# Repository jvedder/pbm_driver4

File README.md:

# pdm_driver4_v1

PCB Design in KiCad 7 with 4 channels of high-speed, current-controlled LED drivers for a PBM Device prototype. 

**MIT License**

**WARNING**: The eye safety of this device has not been established. **USE AT YOUR OWN RISK.**

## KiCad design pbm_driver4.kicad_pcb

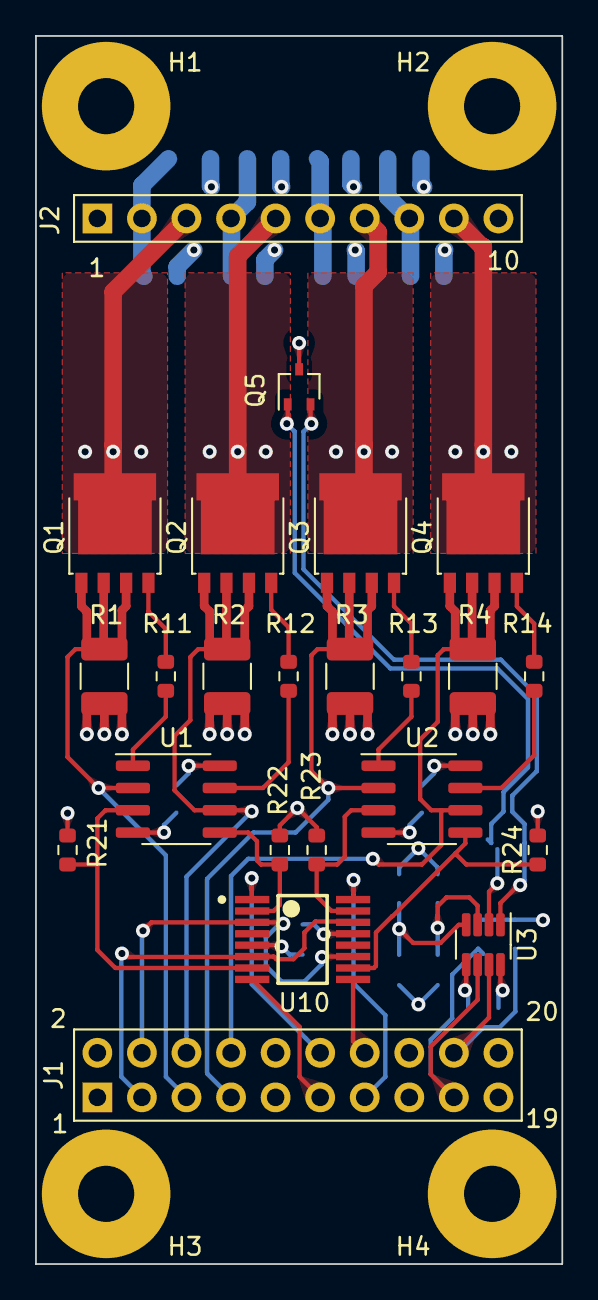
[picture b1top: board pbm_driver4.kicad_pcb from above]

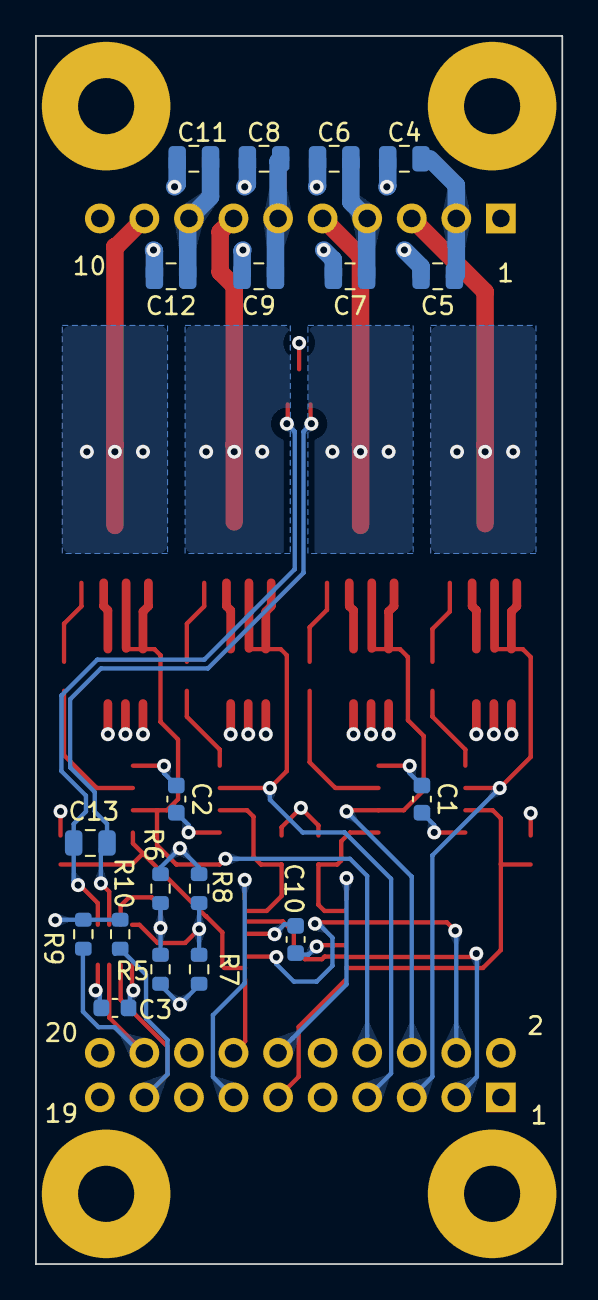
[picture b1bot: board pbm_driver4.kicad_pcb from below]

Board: 4 copper layers, 30.0 x 70.0 mm, 46 parts (19 on the bottom side), 35 nets.

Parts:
C1, C2, C3, C10: 0.1uF; C_0603_1608Metric
C4, C5, C6, C7, C8, C9, C11, C12: 10uF; C_0805_2012Metric
C13: 100pF; C_0805_2012Metric
H1, H2, H3, H4: MountingHole_Pad; MountingHole_3.2mm_M3_Pad
J1: Conn_02x10_Odd_Even; PinHeader_2x10_P2.54mm_Vertical
J2: Conn_01x10; PinHeader_1x10_P2.54mm_Vertical
Q1, Q2, Q3, Q4: PSMN4R0-30YLD; LFPAK56
Q5: MMBT3906; SOT-323_SC-70
R1, R2, R3, R4: 0.510; R_1210_3225Metric_Pad1.30x2.65mm_HandSolder
R5, R6, R7, R8, R9, R10: 10K; R_0603_1608Metric
R11, R12, R13, R14: 100; R_0603_1608Metric
R21, R22, R23, R24: 100K; R_0603_1608Metric
U1, U2: ADA4099-2; SOIC-8_3.9x4.9mm_P1.27mm
U3: TMP421; SOT-23-8
U10: TMUX1112PWR; PW0016A-IPC_A

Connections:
+3.3V: C3.1, C10.1, J1.20, R5.1, R7.1, R9.1, R10.1, U3.8 (V+), U10.13 (VDD)
+12V: C1.1, C2.1, C4.1, C5.1, C6.1, C7.1, C8.1, C9.1, C11.1, C12.1, J1.2, J2.2, J2.4, J2.6, J2.8, U1.8 (V+), U2.8 (V+)
/DAC1: J1.3, U10.6 (S4), U10.14 (S2)
/DAC2: J1.4, U10.3 (S1), U10.11 (S3)
/I2C_SCL: J1.17, R10.2, U3.6 (SDA)
/I2C_SDA: J1.18, R9.2, U3.7 (SCL)
/LED1: J2.3, Q1.5 (D)
/LED2: J2.5, Q2.5 (D)
/LED3: J2.7, Q3.5 (D)
/LED4: J2.9, Q4.5 (D)
/SEL1: J1.11, U10.8 (SEL4)
/SEL2: J1.12, U10.1 (SEL1)
/SEL3: J1.13, U10.16 (SEL2)
/SEL4: J1.14, U10.9 (SEL3)
/SENSE1: J1.5, Q1.1 (S), Q1.2 (S), Q1.3 (S), R1.1, U1.2 (-)
/SENSE2: J1.6, Q2.1 (S), Q2.2 (S), Q2.3 (S), R2.1, U1.6 (-)
/SENSE3: J1.7, Q3.1 (S), Q3.2 (S), Q3.3 (S), R3.1, U2.2 (-)
/SENSE4: J1.8, Q4.1 (S), Q4.2 (S), Q4.3 (S), R4.1, U2.6 (-)
/Sheet 2/REF1: R21.1, U1.3 (+), U10.7 (D4)
/Sheet 2/REF2: R22.1, U1.5 (+), U10.2 (D1)
/Sheet 2/REF3: R23.1, U2.3 (+), U10.15 (D2)
/Sheet 2/REF4: R24.1, U2.5 (+), U10.10 (D3)
/Sheet 5/A0: R7.2, R8.1, U3.4 (A0)
/Sheet 5/A1: R5.2, R6.1, U3.3 (A1)
/Sheet 5/DX_N: C13.2, Q5.1 (B), U3.2 (DXN)
/Sheet 5/DX_P: C13.1, Q5.2 (E), U3.1 (DXP)
GND: C1.2, C2.2, C3.2, C4.2, C5.2, C6.2, C7.2, C8.2, C9.2, C10.2, C11.2, C12.2, H1.1, H2.1, H3.1, H4.1, J1.1, J1.9, J1.10, J1.15, J1.16, J1.19, J2.1, J2.10, Q5.3 (C), R1.2, R2.2, R3.2, R4.2, R6.2, R8.2, R21.2, R22.2, R23.2, R24.2, U1.4 (V-), U2.4 (V-), U3.5 (GND), U10.5 (GND)
unnamed: Q1.4 (G), R11.2
unnamed: Q2.4 (G), R12.2
unnamed: Q3.4 (G), R13.2
unnamed: Q4.4 (G), R14.2
unnamed: R11.1, U1.1
unnamed: R12.1, U1.7
unnamed: R13.1, U2.1
unnamed: R14.1, U2.7

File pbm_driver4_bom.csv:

"Source:","C:\Users\John\Documents\KiCAD\7.0\projects\pbm_driver4\pbm_driver4.kicad_sch"
"Date:","2/19/2024 8:24:11 PM"
"Tool:","Eeschema 7.0.9"
"Generator:","C:\Program Files\KiCad\7.0\bin\scripting\plugins/bom_csv_grouped_by_value_with_fp.py"
"Component Count:","46"
"Ref","Qnty","Value","Cmp name","Footprint","Description","Vendor","DNP"
"C1, C2, C3, C10","4","0.1uF","C","$Local:C_0603_1608Metric","Unpolarized capacitor","",""
"C4, C5, C6, C7, C8, C9, C11, C12","8","10uF","C","$Local:C_0805_2012Metric","Unpolarized capacitor","",""
"C13","1","100pF","C","$Local:C_0805_2012Metric","Unpolarized capacitor","",""
"H1, H2, H3, H4","4","MountingHole_Pad","MountingHole_Pad","$Local:MountingHole_3.2mm_M3_Pad","Mounting Hole with connection","",""
"J1","1","Conn_02x10_Odd_Even","Conn_02x10_Odd_Even","$Local:PinHeader_2x10_P2.54mm_Vertical","Generic connector, double row, 02x10, odd/even pin numbering scheme (row 1 odd numbers, row 2 even numbers), script generated (kicad-library-utils/schlib/autogen/connector/)","",""
"J2","1","Conn_01x10","Conn_01x10","$Local:PinHeader_1x10_P2.54mm_Vertical","Generic connector, single row, 01x10, script generated (kicad-library-utils/schlib/autogen/connector/)","",""
"Q1, Q2, Q3, Q4","4","PSMN4R0-30YLD","PSMN5R2-60YL","$Local:LFPAK56","100A, 60V Vds, N-Channel MOSFET, 5.2mOhm Ron, LFPAK56","Nexperia",""
"Q5","1","MMBT3906","MMBT3906","$Local:SOT-323_SC-70","-0.2A Ic, -40V Vce, Small Signal PNP Transistor, SOT-23","",""
"R1, R2, R3, R4","4","0.510","R_US","$Local:R_1210_3225Metric_Pad1.30x2.65mm_HandSolder","Resistor, US symbol","",""
"R5, R6, R7, R8, R9, R10","6","10K","R_US","$Local:R_0603_1608Metric","Resistor, US symbol","",""
"R11, R12, R13, R14","4","100","R_US","$Local:R_0603_1608Metric","Resistor, US symbol","",""
"R21, R22, R23, R24","4","100K","R_US","$Local:R_0603_1608Metric","Resistor, US symbol","",""
"U1, U2","2","ADA4099-2","Opamp_Dual","$Local:SOIC-8_3.9x4.9mm_P1.27mm","Dual operational amplifier","",""
"U3","1","TMP421","TMP421","$Local:SOT-23-8","Remote and Local Temperature Sensor, I2C, SOT-23-8","",""
"U10","1","TMUX1112PWR","TMUX1112PWR","$Local:PW0016A-IPC_A","","",""

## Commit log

2024-02-10 Clone driver x4 from initial device design.
2024-02-20 As released to fab PCB103_RevA
2024-02-20 Fix typo in README
2024-09-21 Add rework drawings
2024-09-21 Add schematic markup
2025-08-12 Rename project from pbm_driver4 to pbm_driver4_v1
2025-08-12 Update README.md and LICENSE files
